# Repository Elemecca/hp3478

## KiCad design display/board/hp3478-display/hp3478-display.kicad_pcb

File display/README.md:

## MCAD <-> ECAD Workflow

### Digit Legend Symbols

1. Open `3478A_display.FCStd` in FreeCAD
2. Activate the TechDraw workspace
3. Select the appropriate page in the "Shape Export Pages" group
4. In the TechDraw menu, select "Export Page as SVG"
5. Open the SVG in Inkscape and export as PNG at 6000 pixels square
6. Open the `hp3478-display` project in KiCAD
7. Open the Image Converter tool, load the PNG, and export to a symbol file
8. Open the Symbol Editor tool and select the `0Local` library
9. Import the generated symbol file, copy and paste its graphics elements
   into the target symbol, and delete the imported symbol
10. Delete the imported colon and comma segments
11. Position the imported segments over the old segments
12. Remove the old segments
13. Save the symbol and update all matching symbols in the schematic

### Digit Outline Footprint

1. Open `3478A_display.FCStd` in FreeCAD
2. Activate the TechDraw workspace
3. Select the appropriate page in the "Shape Export Pages" group
4. In the TechDraw menu, select "Export Page as SVG"
5. Open the SVG in Inkscape
6. Select all and ungroup once
7. Turn off the fill paint
8. Set the stroke paint to 0.006" solid black
9. Save the SVG from Inkscape
10. Open the `hp2478-display` project in KiCAD
11. Open the Footprint Editor tool and select `0Local:Digit_Outline`
12. Import the SVG with "File -> Import -> Graphics..."
13. Position the newly imported lines over the old lines
14. Remove the old lines
15. Save the footprint and update all matching footprints in the board

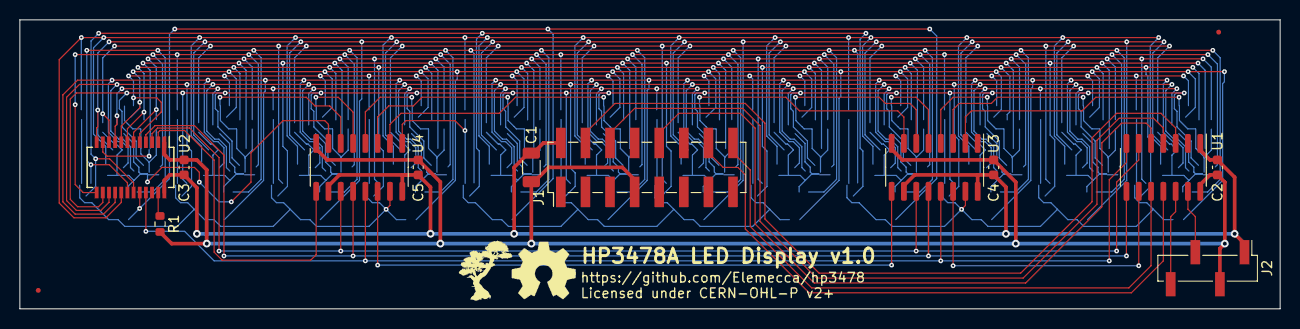
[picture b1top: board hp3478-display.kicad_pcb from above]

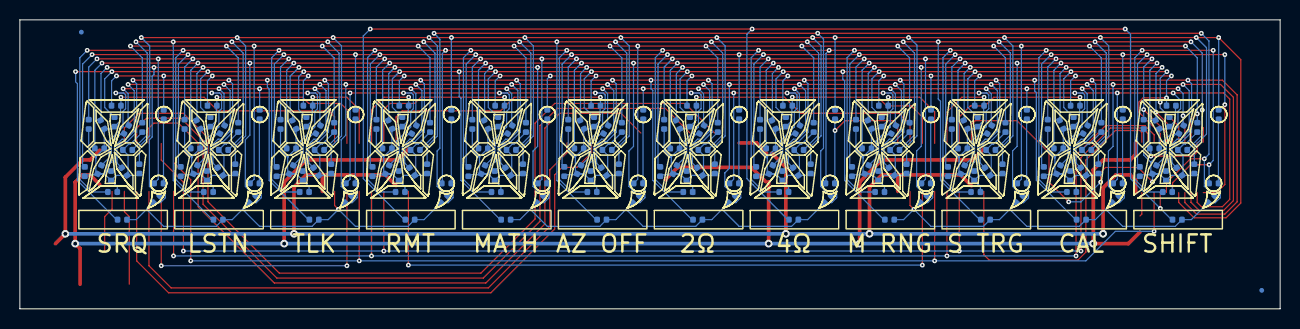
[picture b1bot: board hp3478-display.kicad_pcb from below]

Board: 2 copper layers, 130.2 x 29.8 mm, 244 parts (230 on the bottom side), 47 nets.

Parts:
C1: 22u; C_1206_3216Metric
C2, C3, C4, C5: 100n; C_0603_1608Metric
D101, D102, D103, D104, D105, D106, D107, D108, D109, D110, D111, D112, D113, D114, D115, D116, D117, D118, D119, D120, D121, D122, D123, D124, D125, D126, D127, D128, D129, D130, D131, D132, D133, D134, D135, D136, D137, D138, D139, D140, D141, D142, D143, D144, D145, D146, D147, D148, D201, D202, D203, D204, D205, D206, D207, D208, D209, D210, D211, D212, D213, D214, D301, D302, D303, D304, D305, D306, D307, D308, D309, D310, D311, D312, D313, D314, D401, D402, D403, D404, D405, D406, D407, D408, D409, D410, D411, D412, D413, D414, D501, D502, D503, D504, D505, D506, D507, D508, D509, D510, D511, D512, D513, D514, D601, D602, D603, D604, D605, D606, D607, D608, D609, D610, D611, D612, D613, D614, D701, D702, D703, D704, D705, D706, D707, D708, D709, D710, D711, D712, D713, D714, D801, D802, D803, D804, D805, D806, D807, D808, D809, D810, D811, D812, D813, D814, D901, D902, D903, D904, D905, D906, D907, D908, D909, D910, D911, D912, D913, D914, D1001, D1002, D1003, D1004, D1005, D1006, D1007, D1008, D1009, D1010, D1011, D1012, D1013, D1014, D1101, D1102, D1103, D1104, D1105, D1106, D1107, D1108, D1109, D1110, D1111, D1112, D1113, D1114, D1201, D1202, D1203, D1204, D1205, D1206, D1207, D1208, D1209, D1210, D1211, D1212, D1213, D1214, D1301, D1302, D1303, D1304, D1305, D1306, D1307, D1308, D1309, D1310, D1311, D1312, D1313, D1314: LED; LED_0402_1005Metric
FD1, FD2, FD3, FD4: Fiducial_0.5mm_Mask1.5mm
J1: Header; PinHeader_2x08_P2.54mm_Vertical_SMD
J2: Header; PinHeader_1x04_P2.54mm_Vertical_SMD_Pin1Left
R1: 5k6 1%; R_0603_1608Metric
REF0, REF1, REF2, REF3, REF4, REF5, REF6, REF7, REF8, REF9, REF10, REF11: Value; Digit_Outline
U1: FT60F1x2; SO-14_3.9x8.65mm_P1.27mm
U2: SM16206S; SSOP-24_3.9x8.7mm_P0.635mm
U3, U4: 74HC595; SOIC-16_3.9x9.9mm_P1.27mm

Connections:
+5V: C1.1, C2.1, C3.1, C4.1, C5.1, J1.2, J2.1, U1.1 (VDD), U2.24 (VDD), U3.10 (~SRCLR), U3.16 (VCC), U4.10 (~SRCLR), U4.16 (VCC)
/A0: D101.2 (A), D102.2 (A), D103.2 (A), D104.2 (A), D105.2 (A), D106.2 (A), D107.2 (A), D108.2 (A), D109.2 (A), D110.2 (A), D111.2 (A), D112.2 (A), D113.2 (A), D114.2 (A), D115.2 (A), D116.2 (A), U3.15 (QA)
/A2: D201.2 (A), D202.2 (A), D203.2 (A), D204.2 (A), D205.2 (A), D206.2 (A), D207.2 (A), D208.2 (A), D209.2 (A), D210.2 (A), D211.2 (A), D212.2 (A), D213.2 (A), D214.2 (A), U3.2 (QC)
/A3: D301.2 (A), D302.2 (A), D303.2 (A), D304.2 (A), D305.2 (A), D306.2 (A), D307.2 (A), D308.2 (A), D309.2 (A), D310.2 (A), D311.2 (A), D312.2 (A), D313.2 (A), D314.2 (A), U3.3 (QD)
/A4: D401.2 (A), D402.2 (A), D403.2 (A), D404.2 (A), D405.2 (A), D406.2 (A), D407.2 (A), D408.2 (A), D409.2 (A), D410.2 (A), D411.2 (A), D412.2 (A), D413.2 (A), D414.2 (A), U3.4 (QE)
/A5: D501.2 (A), D502.2 (A), D503.2 (A), D504.2 (A), D505.2 (A), D506.2 (A), D507.2 (A), D508.2 (A), D509.2 (A), D510.2 (A), D511.2 (A), D512.2 (A), D513.2 (A), D514.2 (A), U3.5 (QF)
/A6: D601.2 (A), D602.2 (A), D603.2 (A), D604.2 (A), D605.2 (A), D606.2 (A), D607.2 (A), D608.2 (A), D609.2 (A), D610.2 (A), D611.2 (A), D612.2 (A), D613.2 (A), D614.2 (A), U3.6 (QG)
/A7: D701.2 (A), D702.2 (A), D703.2 (A), D704.2 (A), D705.2 (A), D706.2 (A), D707.2 (A), D708.2 (A), D709.2 (A), D710.2 (A), D711.2 (A), D712.2 (A), D713.2 (A), D714.2 (A), U3.7 (QH)
/A8: D133.2 (A), D134.2 (A), D135.2 (A), D136.2 (A), D137.2 (A), D138.2 (A), D139.2 (A), D140.2 (A), D141.2 (A), D142.2 (A), D143.2 (A), D144.2 (A), D145.2 (A), D146.2 (A), D147.2 (A), D148.2 (A), U4.15 (QA)
/A9: D117.2 (A), D118.2 (A), D119.2 (A), D120.2 (A), D121.2 (A), D122.2 (A), D123.2 (A), D124.2 (A), D125.2 (A), D126.2 (A), D127.2 (A), D128.2 (A), D129.2 (A), D130.2 (A), D131.2 (A), D132.2 (A), U4.1 (QB)
/A10: D801.2 (A), D802.2 (A), D803.2 (A), D804.2 (A), D805.2 (A), D806.2 (A), D807.2 (A), D808.2 (A), D809.2 (A), D810.2 (A), D811.2 (A), D812.2 (A), D813.2 (A), D814.2 (A), U4.2 (QC)
/A11: D901.2 (A), D902.2 (A), D903.2 (A), D904.2 (A), D905.2 (A), D906.2 (A), D907.2 (A), D908.2 (A), D909.2 (A), D910.2 (A), D911.2 (A), D912.2 (A), D913.2 (A), D914.2 (A), U4.3 (QD)
/A12: D1001.2 (A), D1002.2 (A), D1003.2 (A), D1004.2 (A), D1005.2 (A), D1006.2 (A), D1007.2 (A), D1008.2 (A), D1009.2 (A), D1010.2 (A), D1011.2 (A), D1012.2 (A), D1013.2 (A), D1014.2 (A), U4.4 (QE)
/A13: D1101.2 (A), D1102.2 (A), D1103.2 (A), D1104.2 (A), D1105.2 (A), D1106.2 (A), D1107.2 (A), D1108.2 (A), D1109.2 (A), D1110.2 (A), D1111.2 (A), D1112.2 (A), D1113.2 (A), D1114.2 (A), U4.5 (QF)
/A14: D1201.2 (A), D1202.2 (A), D1203.2 (A), D1204.2 (A), D1205.2 (A), D1206.2 (A), D1207.2 (A), D1208.2 (A), D1209.2 (A), D1210.2 (A), D1211.2 (A), D1212.2 (A), D1213.2 (A), D1214.2 (A), U4.6 (QG)
/A15: D1301.2 (A), D1302.2 (A), D1303.2 (A), D1304.2 (A), D1305.2 (A), D1306.2 (A), D1307.2 (A), D1308.2 (A), D1309.2 (A), D1310.2 (A), D1311.2 (A), D1312.2 (A), D1313.2 (A), D1314.2 (A), U4.7 (QH)
/DLC: U1.8 (PC1), U2.4 (LE), U3.12 (RCLK), U4.12 (RCLK)
/DSC: U1.6 (CLKO/PC5), U2.3 (CLK), U3.11 (SRCLK), U4.11 (SRCLK)
/DSD: U1.9 (PC0), U3.14 (SER)
/DSD2: U3.9 (QH'), U4.14 (SER)
/DSD3: U2.2 (SDI), U4.9 (QH')
/K0: D101.1 (K), D117.1 (K), D133.1 (K), D201.1 (K), D301.1 (K), D401.1 (K), D501.1 (K), D601.1 (K), D701.1 (K), D801.1 (K), D901.1 (K), D1001.1 (K), D1101.1 (K), D1201.1 (K), D1301.1 (K), U2.5 (OUT0)
/K1: D102.1 (K), D118.1 (K), D134.1 (K), D202.1 (K), D302.1 (K), D402.1 (K), D502.1 (K), D602.1 (K), D702.1 (K), D802.1 (K), D902.1 (K), D1002.1 (K), D1102.1 (K), D1202.1 (K), D1302.1 (K), U2.6 (OUT1)
/K2: D103.1 (K), D119.1 (K), D135.1 (K), D203.1 (K), D303.1 (K), D403.1 (K), D503.1 (K), D603.1 (K), D703.1 (K), D803.1 (K), D903.1 (K), D1003.1 (K), D1103.1 (K), D1203.1 (K), D1303.1 (K), U2.7 (OUT2)
/K3: D104.1 (K), D120.1 (K), D136.1 (K), D204.1 (K), D304.1 (K), D404.1 (K), D504.1 (K), D604.1 (K), D704.1 (K), D804.1 (K), D904.1 (K), D1004.1 (K), D1104.1 (K), D1204.1 (K), D1304.1 (K), U2.8 (OUT3)
/K4: D105.1 (K), D121.1 (K), D137.1 (K), D205.1 (K), D305.1 (K), D405.1 (K), D505.1 (K), D605.1 (K), D705.1 (K), D805.1 (K), D905.1 (K), D1005.1 (K), D1105.1 (K), D1205.1 (K), D1305.1 (K), U2.9 (OUT4)
/K5: D106.1 (K), D122.1 (K), D138.1 (K), D206.1 (K), D306.1 (K), D406.1 (K), D506.1 (K), D606.1 (K), D706.1 (K), D806.1 (K), D906.1 (K), D1006.1 (K), D1106.1 (K), D1206.1 (K), D1306.1 (K), U2.10 (OUT5)
/K6: D107.1 (K), D123.1 (K), D139.1 (K), D207.1 (K), D307.1 (K), D407.1 (K), D507.1 (K), D607.1 (K), D707.1 (K), D807.1 (K), D907.1 (K), D1007.1 (K), D1107.1 (K), D1207.1 (K), D1307.1 (K), U2.11 (OUT6)
/K7: D108.1 (K), D124.1 (K), D140.1 (K), D208.1 (K), D308.1 (K), D408.1 (K), D508.1 (K), D608.1 (K), D708.1 (K), D808.1 (K), D908.1 (K), D1008.1 (K), D1108.1 (K), D1208.1 (K), D1308.1 (K), U2.12 (OUT7)
/K8: D109.1 (K), D125.1 (K), D141.1 (K), D209.1 (K), D309.1 (K), D409.1 (K), D509.1 (K), D609.1 (K), D709.1 (K), D809.1 (K), D909.1 (K), D1009.1 (K), D1109.1 (K), D1209.1 (K), D1309.1 (K), U2.13 (OUT8)
/K9: D110.1 (K), D126.1 (K), D142.1 (K), D210.1 (K), D310.1 (K), D410.1 (K), D510.1 (K), D610.1 (K), D710.1 (K), D810.1 (K), D910.1 (K), D1010.1 (K), D1110.1 (K), D1210.1 (K), D1310.1 (K), U2.14 (OUT9)
/K10: D111.1 (K), D127.1 (K), D143.1 (K), D211.1 (K), D311.1 (K), D411.1 (K), D511.1 (K), D611.1 (K), D711.1 (K), D811.1 (K), D911.1 (K), D1011.1 (K), D1111.1 (K), D1211.1 (K), D1311.1 (K), U2.15 (OUT10)
/K11: D112.1 (K), D128.1 (K), D144.1 (K), D212.1 (K), D312.1 (K), D412.1 (K), D512.1 (K), D612.1 (K), D712.1 (K), D812.1 (K), D912.1 (K), D1012.1 (K), D1112.1 (K), D1212.1 (K), D1312.1 (K), U2.16 (OUT11)
/K12: D113.1 (K), D129.1 (K), D145.1 (K), D213.1 (K), D313.1 (K), D413.1 (K), D513.1 (K), D613.1 (K), D713.1 (K), D813.1 (K), D913.1 (K), D1013.1 (K), D1113.1 (K), D1213.1 (K), D1313.1 (K), U2.17 (OUT12)
/K13: D114.1 (K), D130.1 (K), D146.1 (K), D214.1 (K), D314.1 (K), D414.1 (K), D514.1 (K), D614.1 (K), D714.1 (K), D814.1 (K), D914.1 (K), D1014.1 (K), D1114.1 (K), D1214.1 (K), D1314.1 (K), U2.18 (OUT13)
/K14: D115.1 (K), D131.1 (K), D147.1 (K), U2.19 (OUT14)
/K15: D116.1 (K), D132.1 (K), D148.1 (K), U2.20 (OUT15)
/LCD_ISA: J1.4, U1.3 (PA6)
/LCD_IWA: J1.10, U1.5 (PA4)
/LCD_P1: J1.14, U1.11 (PA2/T0CKI/INT)
/LCD_PWO: J1.16, U1.10 (PA3)
/LCD_SYNC: J1.6, U1.4 (PA5/~MCLR)
/PGC: J2.3, U1.13 (ISPCLK/PA0)
/PGD: J2.4, U1.12 (ISPDAT/PA1)
/~DOE: U1.7 (PC4), U2.21 (~OE), U3.13 (~OE), U4.13 (~OE)
GND: C1.2, C2.2, C3.2, C4.2, C5.2, J1.7, J2.2, R1.2, U1.14 (GND), U2.1 (GND), U3.8 (GND), U4.8 (GND)
unnamed: R1.1, U2.23 (R-EXT)

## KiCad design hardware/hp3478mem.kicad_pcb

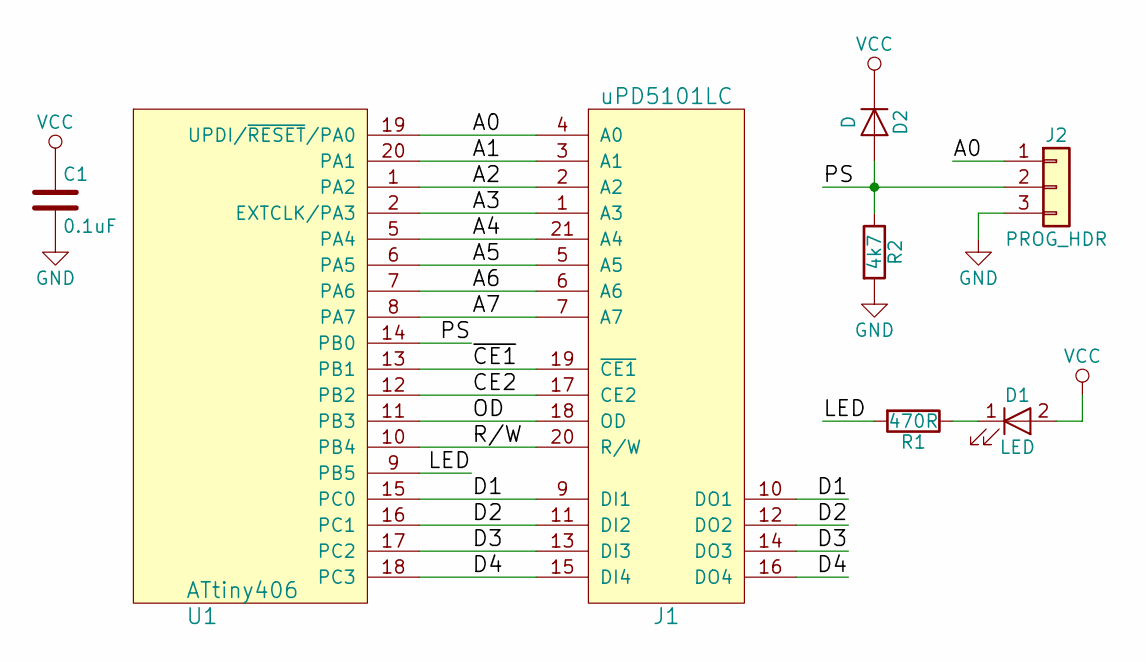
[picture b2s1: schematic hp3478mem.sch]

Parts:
C1: 0.1uF; C_0805
D1: LED; LED_0805
D2: D; D_MiniMELF
J1: uPD5101LC; DIP-22_W10.16mm
J2: PROG_HDR; Pin_Header_Straight_1x03_Pitch2.54mm
R1: 470R; R_0805
R2: 4k7; R_0805
U1: ATtiny406; UQFN-20-1EP_3x3mm_Pitch0.4mm

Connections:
/A0: J1.4 (A0), J2.1, U1.19 (UPDI/~RESET~/PA0)
/A1: J1.3 (A1), U1.20 (PA1)
/A2: J1.2 (A2), U1.1 (PA2)
/A3: J1.1 (A3), U1.2 (EXTCLK/PA3)
/A4: J1.21 (A4), U1.5 (PA4)
/A5: J1.5 (A5), U1.6 (PA5)
/A6: J1.6 (A6), U1.7 (PA6)
/A7: J1.7 (A7), U1.8 (PA7)
/CE2: J1.17 (CE2), U1.12 (PB2)
/D1: J1.9 (DI1), J1.10 (DO1), U1.15 (PC0)
/D2: J1.11 (DI2), J1.12 (DO2), U1.16 (PC1)
/D3: J1.13 (DI3), J1.14 (DO3), U1.17 (PC2)
/D4: J1.15 (DI4), J1.16 (DO4), U1.18 (PC3)
/LED: R1.2, U1.9 (PB5)
/OD: J1.18 (OD), U1.11 (PB3)
/PS: D2.2 (A), J2.2, R2.1, U1.14 (PB0)
/R/W: J1.20 (R/W), U1.10 (PB4)
/~CE1: J1.19 (~CE1), U1.13 (PB1)
GND: C1.2, J1.8 (GND), J2.3, R2.2, U1.3 (GND)
unnamed: D1.1 (K), R1.1
VCC: C1.1, D1.2 (A), D2.1 (K), J1.22 (VCC), U1.4 (VCC)

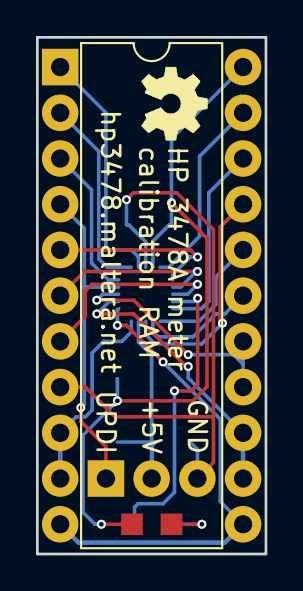
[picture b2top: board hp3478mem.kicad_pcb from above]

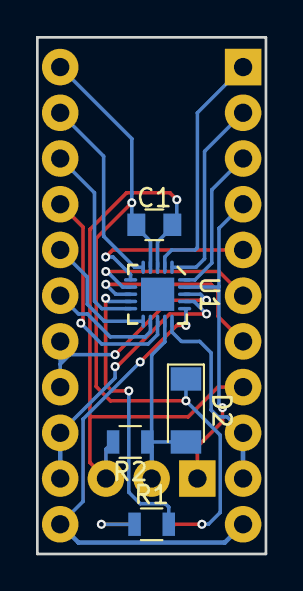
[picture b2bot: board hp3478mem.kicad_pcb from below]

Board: 2 copper layers, 12.7 x 28.7 mm, 9 parts (5 on the bottom side), 21 nets.

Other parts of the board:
OSHW: LOGO; OSHW

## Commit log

2018-06-21 Add initial rev of the board.
2018-07-10 Update pad sizes based on issues with prototypes.
2018-07-10 Add more silkscreen labels.
2022-09-06 Start FreeCAD file for original display.
2022-09-06 Add entire bottom half of digit.
2022-09-06 Add a segment, clean up tangent constraints.
2022-09-06 Add remaining digit segments.
2022-09-06 Mostly fix digit right-side alignment.
2022-09-17 Fully constrain digit sketch.
2022-09-17 Add 2D projection of display.
2022-09-17 Move memory into multi-project format.
2022-09-18 Set segment web with spreadsheet.
2022-10-05 Add display board with microcontroller.
2022-10-05 Clean up DNP alternate footprint for PIC.
2022-10-05 Assign all pins.
2022-10-05 Add digits to board.
2022-10-05 Reorganize schematic.
2022-10-06 Add digit outlines and place LEDs.
2022-10-06 Route LED anode bus.
2022-10-06 Route LED cathode nets.
2022-10-06 Route inputs and MCU support nets.
2022-10-06 Add mounting holes and fiducials.
2022-10-09 Remove MCU and move annunciator LEDs to their own matrix row.
2022-10-11 Swap out MCU and add high-side driver.
2022-12-11 Add missing colon segment and adjust scan matrix.
2022-12-15 Improve workflow for getting digit shapes into KiCAD.
2023-05-18 Clean up some routing.
2023-05-20 Add cathode drivers.
2023-05-22 Move silkscreen clear of vias.
2023-05-22 Add translated SM16206 datasheet.
2023-05-22 Swap anode and cathode - SM16206 is a low-side driver.
2023-05-25 Choose LEDs and set drive current.
2023-05-25 Move datasheets to the root of the display project.
2023-05-25 Add FT60F121 datasheet.
2023-05-25 Swap LCD_P1 and LCD_PWO on MCU so P1 can have edge-triggered interrupts.
2023-05-26 Add trivial test firmware using FMD IDE.
2023-05-27 Implement most of sending LCD commands.
2023-05-27 LCD control mostly working.
2023-05-28 LCD refreshes at 30 Hz.
2023-05-29 Tool to dump display traffic with an FT232H.
2023-05-30 Map the characters supported by the display.
2023-05-30 Figure out the display protocol.
2023-05-30 Attempt to handle host protocol.
2023-05-30 Don't use interrupt-on-change, annunciators and dots work.
2023-05-30 Fix decoding of digits.
2023-05-30 Fix annunciator buffer overrun.
2023-05-30 Use custom LCD characters for extras.
2023-05-31 Fix whitespace.
2023-05-31 Rearrange protocol testing info.
2023-05-31 Semicolon doesn't combine.
2023-05-31 Switch to Microchip mnemonics.

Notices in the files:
display/board/hp3478-display/hp3478-display.kicad_pcb:
© 2022 Sam Hanes, licensed under CERN-OHL-P v2+
